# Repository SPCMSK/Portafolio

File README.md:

# Portfolio de Ingeniería | Matias Ignacio Izaurieta Fernandez

Ingeniero Civil Electrónico (PUCV) | Embedded Systems & Prototipado IoT

## Perfil y Enfoque

Soy un estudiante de 6to año de Ingeniería Civil Electrónica de la Pontificia Universidad Católica de Valparaíso (PUCV). Mi enfoque principal se centra en el **diseño de hardware, los sistemas embebidos y la implementación de soluciones IoT**.

Me considero un profesional en formación con un marcado espíritu **autodidacta** y **"Maker"**. Este repositorio busca demostrar mi habilidad para llevar proyectos desde el concepto hasta el prototipo funcional, combinando programación de firmware (C++/ESP32) con diseño de circuitos y desarrollo de interfaces web.

## Stack Tecnológico Principal

| Categoría | Tecnologías Clave |
| :--- | :--- |
| **Firmware/Hardware** | ESP32, Arduino, C++, KiCad (Diseño PCB & 3D), Eagle, Soldadura. |
| **Programación/Software**| Next.js, TypeScript, JavaScript, Python, TailwindCSS, MATLAB. |
| **Comunicaciones/IoT** | ArtNet, MIDI, Protocolos de Red (WiFi), Impresión 3D. |

## Proyectos Destacados

### 🌐 Desarrollo Web (Fullstack & UI)

#### 1. [SSTransportes.cl](https://sstransportes.cl)
* **Descripción:** Plataforma corporativa para servicios logísticos y transporte. Implementada con un enfoque en rendimiento y escalabilidad, utilizando un stack moderno para una gestión de datos eficiente.
* **Stack:** Next.js, TypeScript, TailwindCSS.
* **Skills Clave:** Optimización de UI/UX, Despliegue (Vercel/Cloud), Tipado estricto para robustez del sitio.

#### 2. [Impcore.cl](https://www.impcore.cl/)
* **Descripción:** Creación y despliegue de una plataforma web completa de difusión musical. Muestra experiencia en el desarrollo Front-End con tecnología moderna, esencial para la visualización de datos en proyectos IoT.
* **Skills Clave:** Next.js, TypeScript, TailwindCSS.

---

### 🎹 Electrónica y Hardware (Eurorack / Audio Analógico)

He desarrollado módulos de síntesis analógica enfocados en la precisión y la integración de componentes de grado de audio, utilizando **KiCad** para el diseño de PCBs, incluyendo modelado 3D de los componentes para asegurar la integridad mecánica del hardware.

#### 3. VCO Austral (Basado en AS3340)
* **Descripción:** Oscilador controlado por voltaje de alta fidelidad. Utiliza el chip **AS3340** para garantizar un seguimiento de octava (V/Oct) extremadamente estable y formas de onda puras (Seno, Triángulo, Sierra, Pulso).
* **Capacidades:** Implementación de compensación térmica y diseño de rutas de señal de bajo ruido.

#### 4. Narcotic VCO (Basado en SSI2130)
* **Descripción:** Diseño avanzado de oscilador utilizando el chip de última generación **SSI2130**. Este proyecto demuestra mi capacidad para trabajar con circuitos integrados complejos de montaje superficial (SMD) que requieren una gestión de señales analógicas y digitales integrada.
* **Capacidades:** Diseño de PCB multi-capa en KiCad, integración de modelos 3D para fabricación y optimización de espacio.

---

### 5. SPC-8SEQ: Secuenciador MIDI de Hardware
* **Descripción:** Prototipado integral de un controlador/secuenciador MIDI de 8 pasos. Ciclo completo de desarrollo: desde la ideación y el diseño de la PCB hasta la programación de firmware en C++ para comunicación USB-MIDI de baja latencia con un ESP32.
* **Skills Clave:** C++, ESP32, Diseño PCB, MIDI, Integración de UI (OLED, Encoders).

### 6. Sistema IoT de Iluminación ArtNet
* **Descripción:** Implementación de un sistema inalámbrico de control lumínico. Configuración de nodos basados en ESP32 como receptores del protocolo ArtNet (DMX sobre IP) para la sincronización en tiempo real con software de visuales (Resolume Arena).
* **Skills Clave:** IoT, Protocolos de Red, ArtNet, ESP32, Automatización.

---

## Contacto

Si deseas revisar el CV completo o discutir oportunidades de práctica, no dudes en contactarme:

* **LinkedIn:** [https://de.linkedin.com/](https://de.linkedin.com/) (Actualiza con tu link directo)
* **Correo Electrónico:** Izaurietamatiasignacio@gmail.com

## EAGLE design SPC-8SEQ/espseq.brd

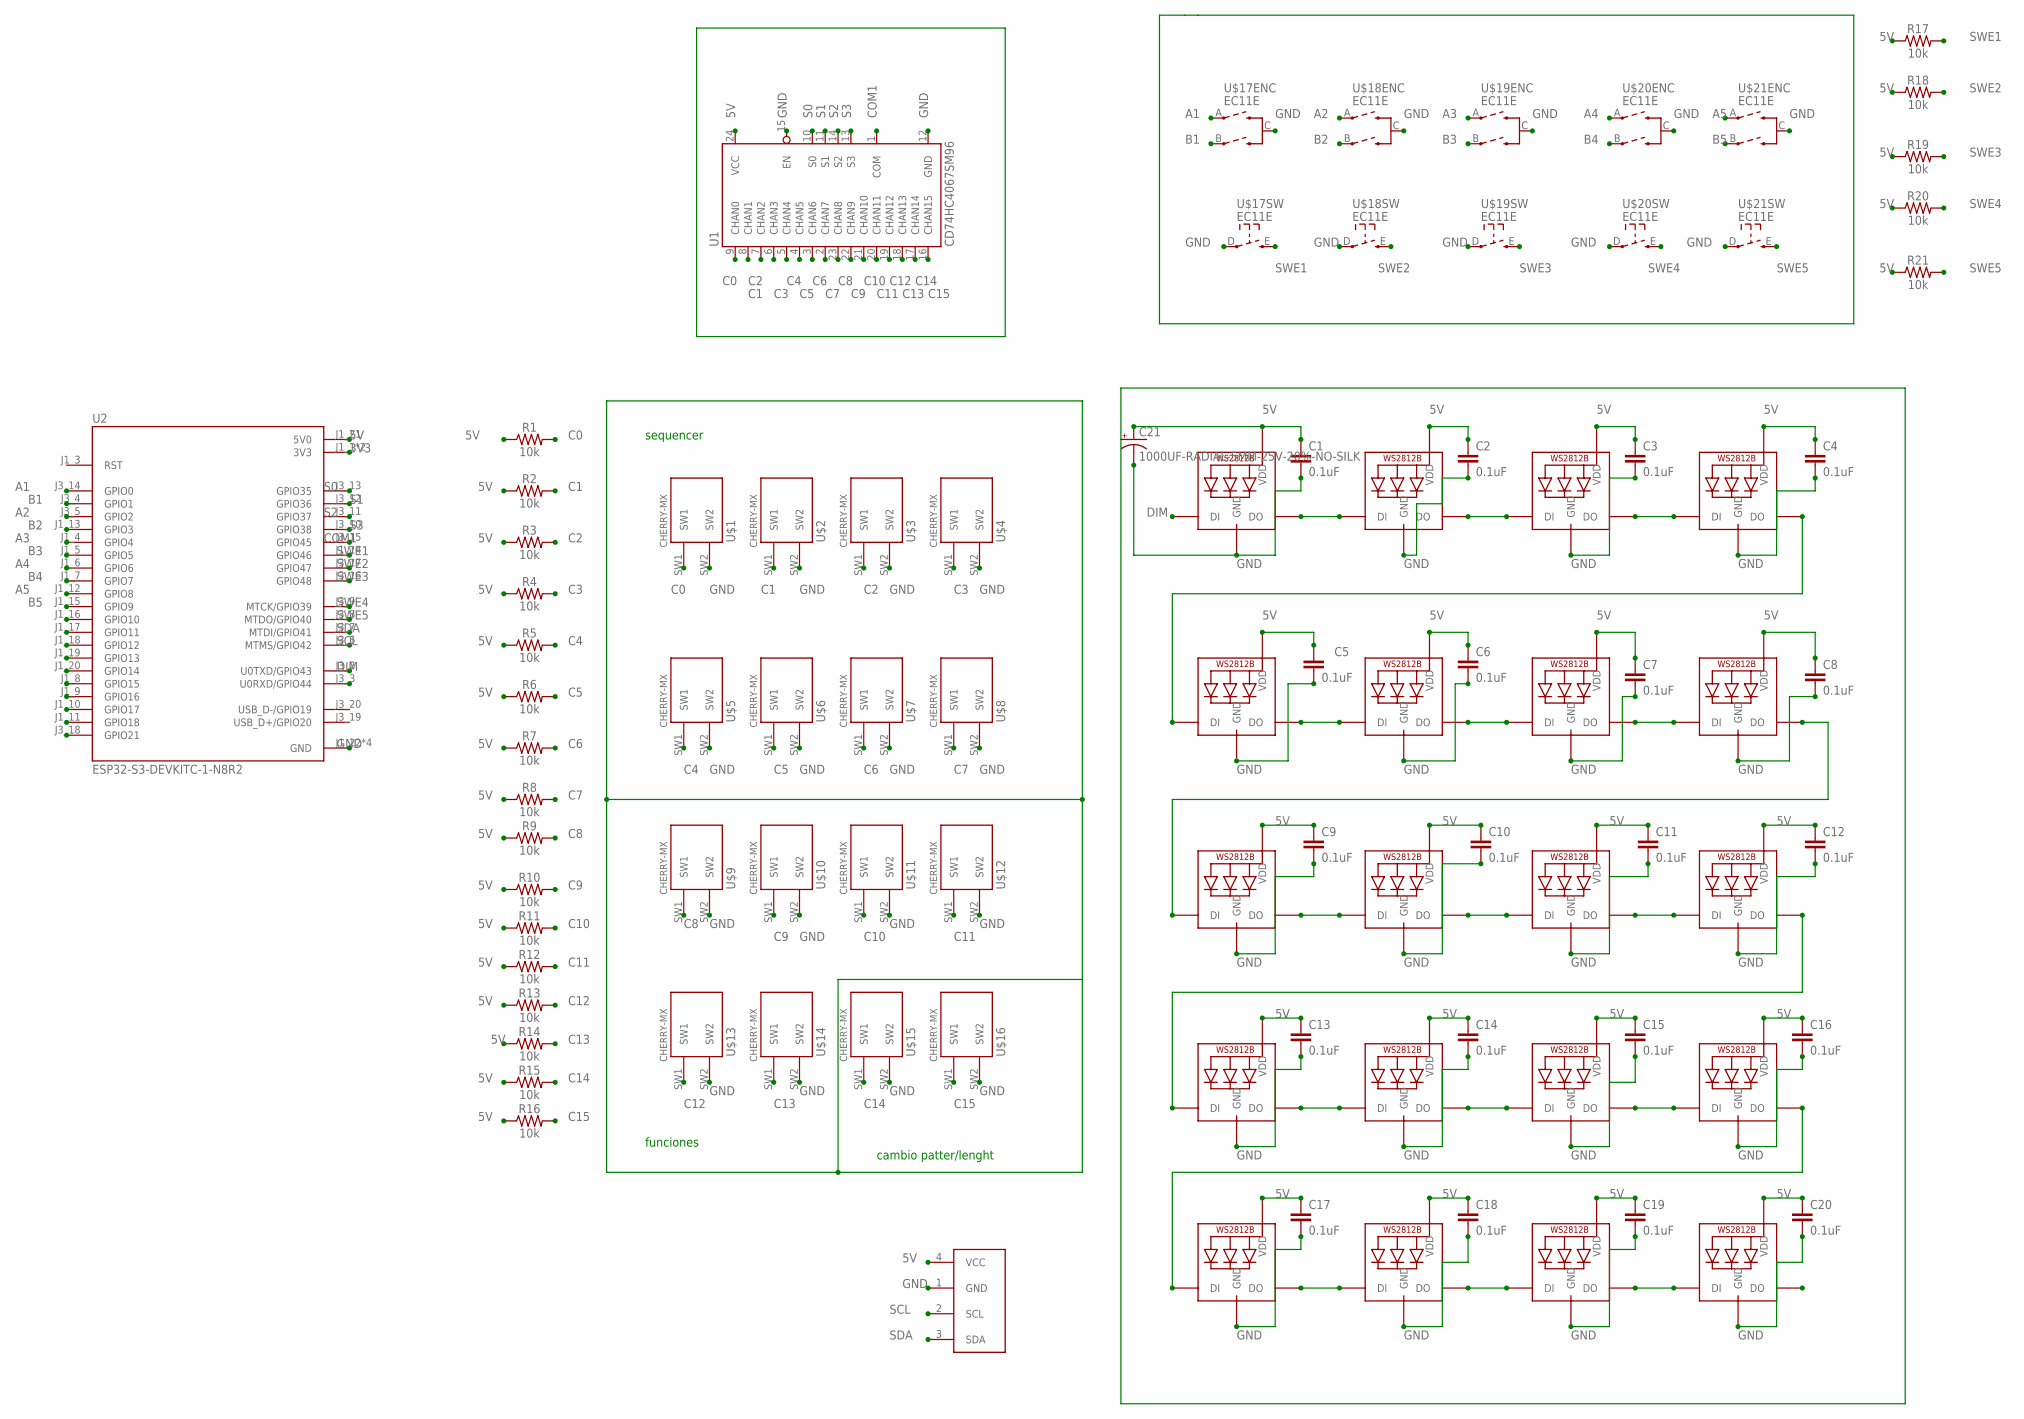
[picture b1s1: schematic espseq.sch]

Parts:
C1, C2, C3, C4, C5, C6, C7, C8, C9, C10, C11, C12, C13, C14, C15, C16, C17, C18, C19, C20: 0.1uF; 0402
C21: 1000UF-RADIAL-5MM-25V-20%-NO-SILK; CPOL-RADIAL-5MM-10MM-NS
LED1, LED2, LED3, LED4, LED5, LED6, LED7, LED8, LED9, LED10, LED11, LED12, LED13, LED14, LED15, LED16, LED17, LED18, LED19, LED20: WS2812B5050; WS2812B
R1, R2, R3, R4, R5, R6, R7, R8, R9, R10, R11, R12, R13, R14, R15, R16, R17, R18, R19, R20, R21: 10k; 0402-TIGHT
U1: CD74HC4067SM96; SSOP24
U2: ESP32-S3-DEVKITC-1-N8R2; XCVR_ESP32-S3-DEVKITC-1-N8R2
U$1, U$2, U$3, U$4, U$5, U$6, U$7, U$8, U$9, U$10, U$11, U$12, U$13, U$14, U$15, U$16: CHERRY-MXSTANDARD; CHERRY-MX
U$17, U$18, U$19, U$20, U$21: EC11E
U$22: I2C_OLED; I2C_OLED_PACKAGE

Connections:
3V3: U2.J1_1 (3V3), U2.J1_2 (3V3)
5V: C1.1, C2.1, C3.1, C4.1, C5.1, C6.1, C7.1, C8.1, C9.1, C10.1, C11.1, C12.1, C13.1, C14.1, C15.1, C16.1, C17.1, C18.1, C19.1, C20.1, C21.+, LED1.1-VDD (VDD), LED2.1-VDD (VDD), LED3.1-VDD (VDD), LED4.1-VDD (VDD), LED5.1-VDD (VDD), LED6.1-VDD (VDD), LED7.1-VDD (VDD), LED8.1-VDD (VDD), LED9.1-VDD (VDD), LED10.1-VDD (VDD), LED11.1-VDD (VDD), LED12.1-VDD (VDD), LED13.1-VDD (VDD), LED14.1-VDD (VDD), LED15.1-VDD (VDD), LED16.1-VDD (VDD), LED17.1-VDD (VDD), LED18.1-VDD (VDD), LED19.1-VDD (VDD), LED20.1-VDD (VDD), R1.1, R2.1, R3.1, R4.1, R5.1, R6.1, R7.1, R8.1, R9.1, R10.1, R11.1, R12.1, R13.1, R14.1, R15.1, R16.1, R17.1, R18.1, R19.1, R20.1, R21.1, U1.24 (VCC), U2.J1_21 (5V0), U$22.4 (VCC)
A1: U2.J3_14 (GPIO0), U$17.A
A2: U2.J3_5 (GPIO2), U$18.A
A3: U2.J1_4 (GPIO4), U$19.A
A4: U2.J1_6 (GPIO6), U$20.A
A5: U2.J1_12 (GPIO8), U$21.A
B1: U2.J3_4 (GPIO1), U$17.B
B2: U2.J1_13 (GPIO3), U$18.B
B3: U2.J1_5 (GPIO5), U$19.B
B4: U2.J1_7 (GPIO7), U$20.B
B5: U2.J1_15 (GPIO9), U$21.B
C0: R1.2, U1.9 (CHAN0), U$1.SW1
C1: R2.2, U1.8 (CHAN1), U$2.SW1
C2: R3.2, U1.7 (CHAN2), U$3.SW1
C3: R4.2, U1.6 (CHAN3), U$4.SW1
C4: R5.2, U1.5 (CHAN4), U$5.SW1
C5: R6.2, U1.4 (CHAN5), U$6.SW1
C6: R7.2, U1.3 (CHAN6), U$7.SW1
C7: R8.2, U1.2 (CHAN7), U$8.SW1
C8: R9.2, U1.23 (CHAN8), U$9.SW1
C9: R10.2, U1.22 (CHAN9), U$10.SW1
C10: R11.2, U1.21 (CHAN10), U$11.SW1
C11: R12.2, U1.20 (CHAN11), U$12.SW1
C12: R13.2, U1.19 (CHAN12), U$13.SW1
C13: R14.2, U1.18 (CHAN13), U$14.SW1
C14: R15.2, U1.17 (CHAN14), U$15.SW1
C15: R16.2, U1.16 (CHAN15), U$16.SW1
COM1: U1.1 (COM), U2.J3_15 (GPIO45)
DIM: LED1.4-DIN (DI), U2.J3_2 (U0TXD/GPIO43)
GND: C1.2, C2.2, C3.2, C4.2, C5.2, C6.2, C7.2, C8.2, C9.2, C10.2, C11.2, C12.2, C13.2, C14.2, C15.2, C16.2, C17.2, C18.2, C19.2, C20.2, C21.-, LED1.3-GND (GND), LED2.3-GND (GND), LED3.3-GND (GND), LED4.3-GND (GND), LED5.3-GND (GND), LED6.3-GND (GND), LED7.3-GND (GND), LED8.3-GND (GND), LED9.3-GND (GND), LED10.3-GND (GND), LED11.3-GND (GND), LED12.3-GND (GND), LED13.3-GND (GND), LED14.3-GND (GND), LED15.3-GND (GND), LED16.3-GND (GND), LED17.3-GND (GND), LED18.3-GND (GND), LED19.3-GND (GND), LED20.3-GND (GND), U1.12 (GND), U1.15 (EN), U2.J1_22 (GND), U2.J3_1 (GND), U2.J3_21 (GND), U2.J3_22 (GND), U$1.SW2, U$2.SW2, U$3.SW2, U$4.SW2, U$5.SW2, U$6.SW2, U$7.SW2, U$8.SW2, U$9.SW2, U$10.SW2, U$11.SW2, U$12.SW2, U$13.SW2, U$14.SW2, U$15.SW2, U$16.SW2, U$17.C, U$17.D (1), U$18.C, U$18.D (1), U$19.C, U$19.D (1), U$20.C, U$20.D (1), U$21.C, U$21.D (1), U$22.1 (GND)
unnamed: LED1.2-DOUT (DO), LED2.4-DIN (DI)
unnamed: LED2.2-DOUT (DO), LED3.4-DIN (DI)
unnamed: LED3.2-DOUT (DO), LED4.4-DIN (DI)
unnamed: LED4.2-DOUT (DO), LED5.4-DIN (DI)
unnamed: LED5.2-DOUT (DO), LED6.4-DIN (DI)
unnamed: LED6.2-DOUT (DO), LED7.4-DIN (DI)
unnamed: LED7.2-DOUT (DO), LED8.4-DIN (DI)
unnamed: LED8.2-DOUT (DO), LED9.4-DIN (DI)
unnamed: LED9.2-DOUT (DO), LED10.4-DIN (DI)
unnamed: LED10.2-DOUT (DO), LED11.4-DIN (DI)
unnamed: LED11.2-DOUT (DO), LED12.4-DIN (DI)
unnamed: LED12.2-DOUT (DO), LED13.4-DIN (DI)
unnamed: LED13.2-DOUT (DO), LED14.4-DIN (DI)
unnamed: LED14.2-DOUT (DO), LED15.4-DIN (DI)
unnamed: LED15.2-DOUT (DO), LED16.4-DIN (DI)
unnamed: LED16.2-DOUT (DO), LED17.4-DIN (DI)
unnamed: LED17.2-DOUT (DO), LED18.4-DIN (DI)
unnamed: LED18.2-DOUT (DO), LED19.4-DIN (DI)
unnamed: LED19.2-DOUT (DO), LED20.4-DIN (DI)
S0: U1.10 (S0), U2.J3_13 (GPIO35)
S1: U1.11 (S1), U2.J3_12 (GPIO36)
S2: U1.14 (S2), U2.J3_11 (GPIO37)
S3: U1.13 (S3), U2.J3_10 (GPIO38)
SCL: U2.J3_6 (MTMS/GPIO42), U$22.2 (SCL)
SDA: U2.J3_7 (MTDI/GPIO41), U$22.3 (SDA)
SWE1: R17.2, U2.J1_14 (GPIO46), U$17.E (3)
SWE2: R18.2, U2.J3_17 (GPIO47), U$18.E (3)
SWE3: R19.2, U2.J3_16 (GPIO48), U$19.E (3)
SWE4: R20.2, U2.J3_9 (MTCK/GPIO39), U$20.E (3)
SWE5: R21.2, U2.J3_8 (MTDO/GPIO40), U$21.E (3)

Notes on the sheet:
cambio patter/lenght
funciones
sequencer

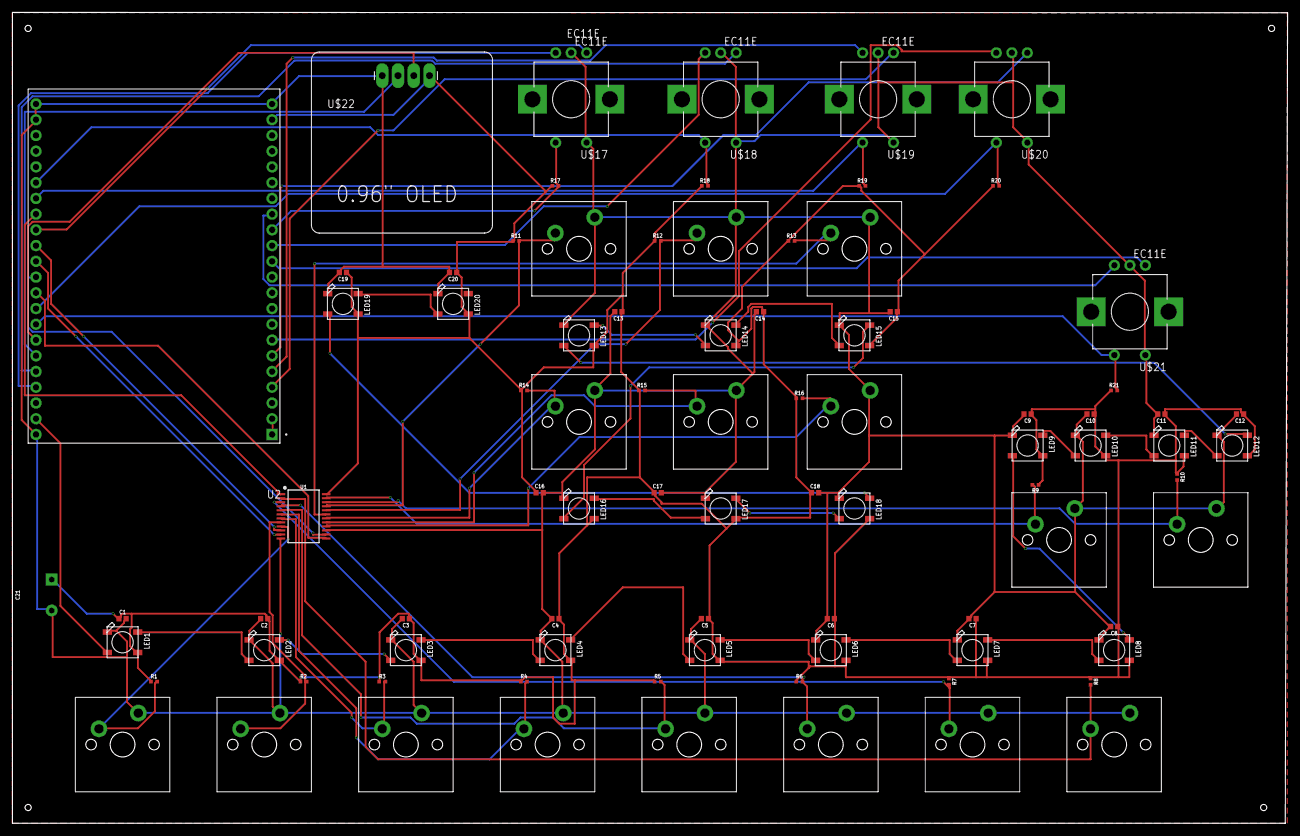
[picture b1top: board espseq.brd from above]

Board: 2 copper layers, 205.8 x 130.9 mm, 86 parts (0 on the bottom side), 61 nets.

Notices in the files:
parts and their libraries:
SparkFun-Capacitors: Licensing: Creative Commons ShareAlike 4.0 International - https://creativecommons.org/licenses/by-sa/4.0
